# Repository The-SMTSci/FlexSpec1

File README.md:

# FlexSpec1

Small telescope Flexible Spectrograph One.

Check out the documentation: 

[FlexSpec1 ReadTheDocs.io](https://flexspec1.readthedocs.io/en/latest/)

History:
--------

V0.0 - pre-release placeholder.

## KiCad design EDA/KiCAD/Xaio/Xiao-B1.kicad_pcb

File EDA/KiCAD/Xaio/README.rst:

Xaio Standalone Board
=====================

Schematics
-----------

KiCAD Files
-----------

* XAIO-B1-A-cache.lib
* XAIO-B1-A-rescue.dcm
* XAIO-B1-A-rescue.lib
* Xiao-B1-cache.lib
* Xiao-B1.kicad_pcb
* Xiao-B1.pro
* Xiao-B1.sch
* Xiao-KM1-a-cache.lib
* Xiao-KM1-a-recover.pro
* Xiao-KM1-a.d356
* Xiao-KM1-a.kicad_pcb
* Xiao-KM1-a.pro
* sym-lib-table

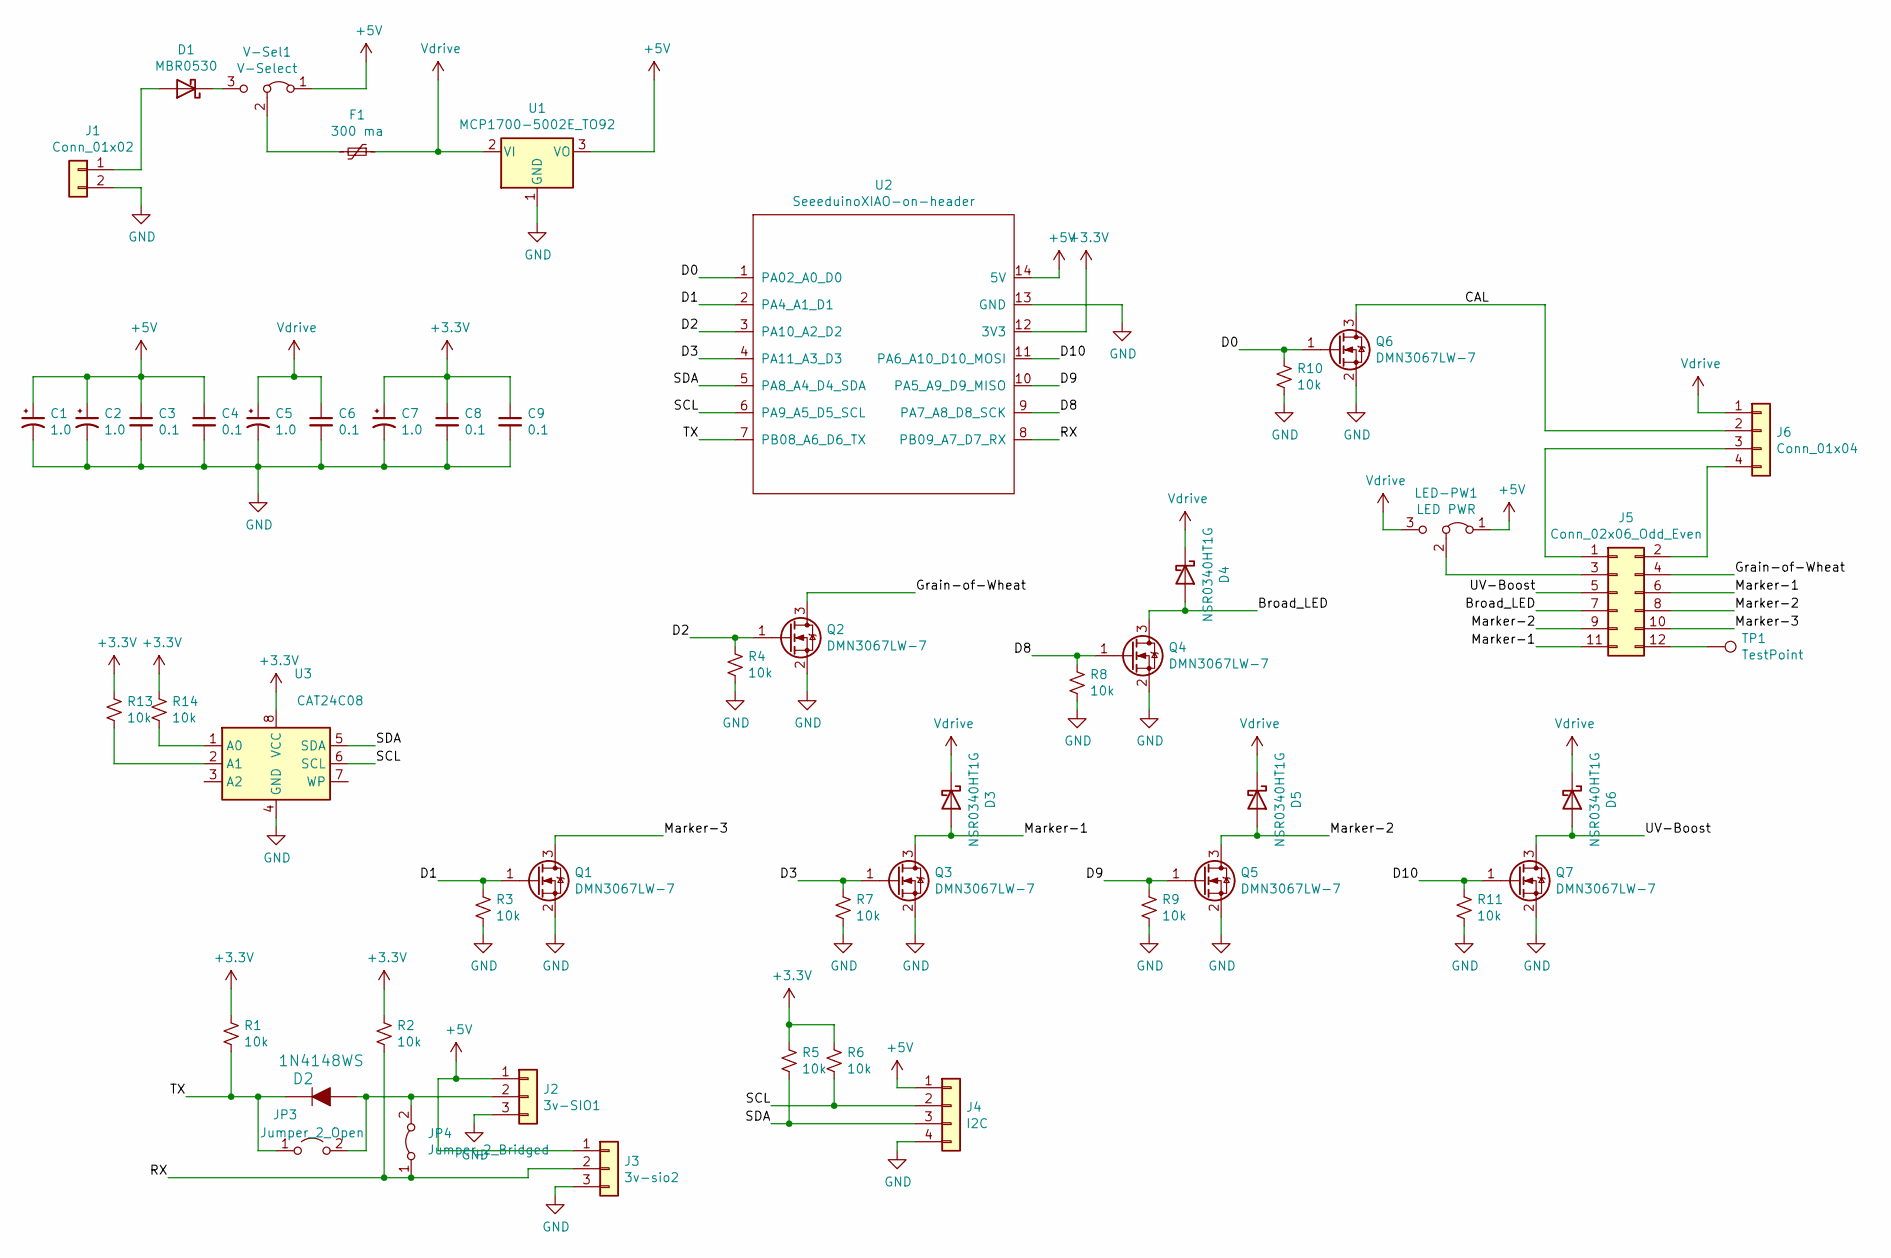
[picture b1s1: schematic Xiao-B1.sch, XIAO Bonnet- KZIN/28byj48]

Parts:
C1, C2, C5, C7: 1.0; C_0805_2012Metric_Pad1.18x1.45mm_HandSolder; MPN CL21A225KAFNNNE; JLCPCB C87994
C3, C4, C6, C8, C9: 0.1; C_0402_1005Metric_Pad0.74x0.62mm_HandSolder; MPN 0402X104K250CT; JLCPCB C237172
D1: MBR0530; D_SOD-123; MPN MBR0530; JLCPCB C475718
D2: 1N4148WS; SOD-323F; MPN 1N4148WS; Digi-Key_PN 1N4148WSFSCT-ND
D3, D4, D5, D6: NSR0340HT1G; D_SOD-323; MPN NSR0340HT1G; JLCPCB C90392
F1: 300 ma; Fuse_0805_2012Metric; MPN 0805L010/24YR; JLCPCB C207019
J1: Conn_01x02; PinHeader_1x02_P2.54mm_Vertical
J2: 3v-SIO1; Hirose_DF13-03P-1.25DSA_1x03_P1.25mm_Vertical; MPN 0530470310; Digi-Key_PN WM1732-ND
J3: 3v-sio2; Hirose_DF13-03P-1.25DSA_1x03_P1.25mm_Vertical; MPN 0530470310; Digi-Key_PN WM1732-ND
J4: I2C; Hirose_DF13-04P-1.25DSA_1x04_P1.25mm_Vertical; MPN 0530470410; Digi-Key_PN WM1733-ND
J5: Conn_02x06_Odd_Even; PinHeader_2x06_P2.54mm_Vertical; Mouser_PN 437-8038701020001101
J6: Conn_01x04; PinHeader_1x04_P2.54mm_Vertical
JP3: Jumper_2_Open; SolderJumper-2_P1.3mm_Open_Pad1.0x1.5mm
JP4: Jumper_2_Bridged; SolderJumper-2_P1.3mm_Bridged_Pad1.0x1.5mm
LED-PW1: LED PWR; SolderJumper-3_P1.3mm_Bridged12_Pad1.0x1.5mm_NumberLabels
Q1, Q2, Q3, Q4, Q5, Q6, Q7: DMN3067LW-7; SOT-323_SC-70_Handsoldering; MPN DMN3067LW-7; JLCPCB C212325
R1, R2, R3, R4, R5, R6, R7, R8, R9, R10, R11, R13, R14: 10k; R_0603_1608Metric_Pad0.98x0.95mm_HandSolder; MPN RC0603FR-0710KL; JLCPCB C98220
TP1: TestPoint; TestPoint_THTPad_1.0x1.0mm_Drill0.5mm
U1: MCP1700-5002E_TO92; TO-92_Inline
U2: SeeeduinoXIAO-on-header; Xiao-on-Header
U3: CAT24C08; TSSOP-8_4.4x3mm_P0.65mm; MPN CAT24C08YI-GT3; JLCPCB C193225
V-Sel1: V-Select; SolderJumper-3_P1.3mm_Bridged12_Pad1.0x1.5mm_NumberLabels

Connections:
+3V3: C7.1, C8.1, C9.1, R1.1, R2.1, R5.1, R6.1, R13.1, R14.1, U2.12 (3V3), U3.8 (VCC)
+5V: C1.1, C2.1, C3.1, C4.1, J2.1, J3.1, J4.1, LED-PW1.1 (A), U1.3 (VO), U2.14 (5V), V-Sel1.1 (A)
/Broad_LED: D4.2 (A), J5.7, Q4.3 (D)
/CAL: J6.2, Q6.3 (D)
/D0: Q6.1 (G), R10.1, U2.1 (PA02_A0_D0)
/D1: Q1.1 (G), R3.1, U2.2 (PA4_A1_D1)
/D2: Q2.1 (G), R4.1, U2.3 (PA10_A2_D2)
/D3: Q3.1 (G), R7.1, U2.4 (PA11_A3_D3)
/D8: Q4.1 (G), R8.1, U2.9 (PA7_A8_D8_SCK)
/D9: Q5.1 (G), R9.1, U2.10 (PA5_A9_D9_MISO)
/D10: Q7.1 (G), R11.1, U2.11 (PA6_A10_D10_MOSI)
/Grain-of-Wheat: J5.4, Q2.3 (D)
/Marker-1: D3.2 (A), J5.6, J5.11, Q3.3 (D)
/Marker-2: D5.2 (A), J5.8, J5.9, Q5.3 (D)
/Marker-3: J5.10, Q1.3 (D)
/RX: J3.2, JP4.1 (A), R2.2, U2.8 (PB09_A7_D7_RX)
/SCL: J4.2, R6.2, U2.6 (PA9_A5_D5_SCL), U3.6 (SCL)
/SDA: J4.3, R5.2, U2.5 (PA8_A4_D4_SDA), U3.5 (SDA)
/TX: D2.K, JP3.1 (A), R1.2, U2.7 (PB08_A6_D6_TX)
/UV-Boost: D6.2 (A), J5.5, Q7.3 (D)
GND: C1.2, C2.2, C3.2, C4.2, C5.2, C6.2, C7.2, C8.2, C9.2, J1.2, J2.3, J3.3, J4.4, Q1.2 (S), Q2.2 (S), Q3.2 (S), Q4.2 (S), Q5.2 (S), Q6.2 (S), Q7.2 (S), R3.2, R4.2, R7.2, R8.2, R9.2, R10.2, R11.2, U1.1 (GND), U2.13 (GND), U3.4 (GND)
unnamed: D1.1 (K), V-Sel1.3 (B)
unnamed: D1.2 (A), J1.1
unnamed: D2.A, J2.2, JP3.2 (B), JP4.2 (B)
unnamed: F1.2, V-Sel1.2 (C)
unnamed: J5.1, J6.3
unnamed: J5.2, J6.4
unnamed: J5.3, LED-PW1.2 (C)
unnamed: J5.12, TP1.1
unnamed: R13.2, U3.2 (A1)
unnamed: R14.2, U3.1 (A0)
Vdrive: C5.1, C6.1, D3.1 (K), D4.1 (K), D5.1 (K), D6.1 (K), F1.1, J6.1, LED-PW1.3 (B), U1.2 (VI)

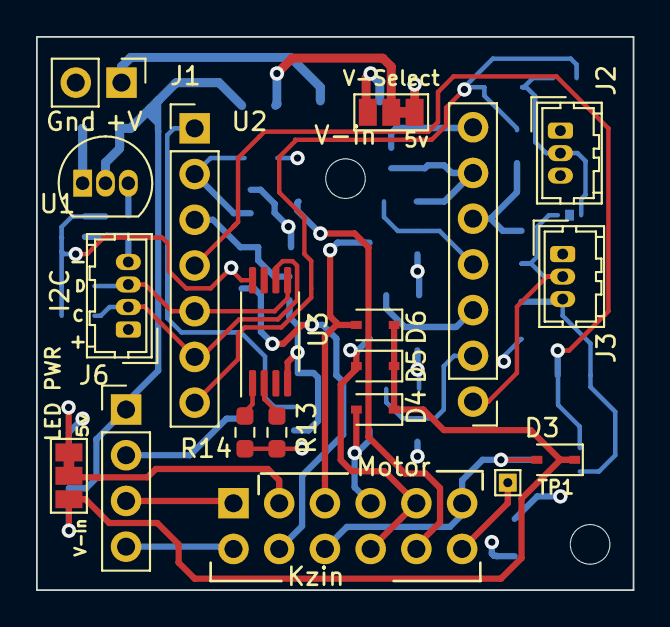
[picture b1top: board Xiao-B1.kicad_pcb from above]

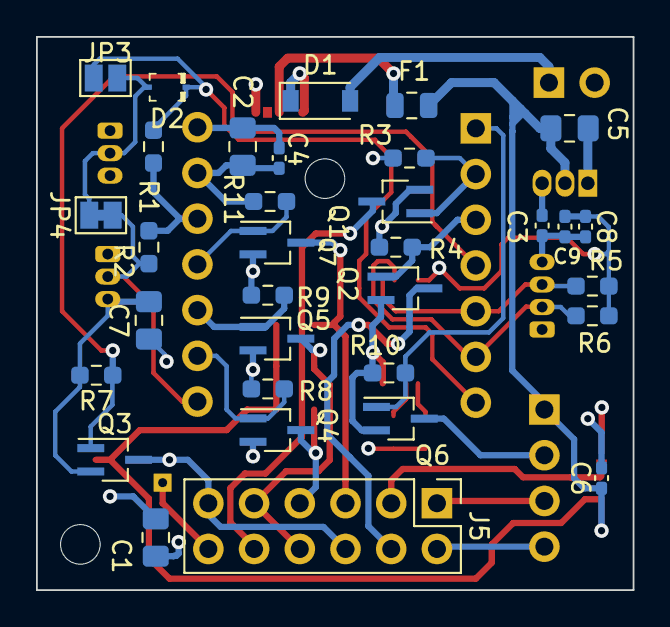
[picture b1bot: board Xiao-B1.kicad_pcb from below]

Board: 4 copper layers, 33.1 x 30.7 mm, 52 parts (33 on the bottom side), 32 nets.

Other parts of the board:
M: MountingHole_2.2mm_M2
M#2: MountingHole_2.2mm_M2

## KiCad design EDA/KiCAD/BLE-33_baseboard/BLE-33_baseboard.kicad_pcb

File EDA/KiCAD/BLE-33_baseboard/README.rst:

EDA BLE-33 Baseboard
====================

Schematics
----------

   * BLE-33_baseboard-v2.pdf
   * BLE-33_baseboard-build-1.pdf

KiCAD Files
-----------

   * BLE-33_baseboard-cache.lib
   * BLE-33_baseboard.d356
   * BLE-33_baseboard.kicad_pcb
   * BLE-33_baseboard.pro
   * BLE-33_baseboard.sch
   * BLE-33_baseboard.step
   * BLE-33_baseboard.wrl
   * Fab_files
   * _autosave-BLE-33_baseboard.pro

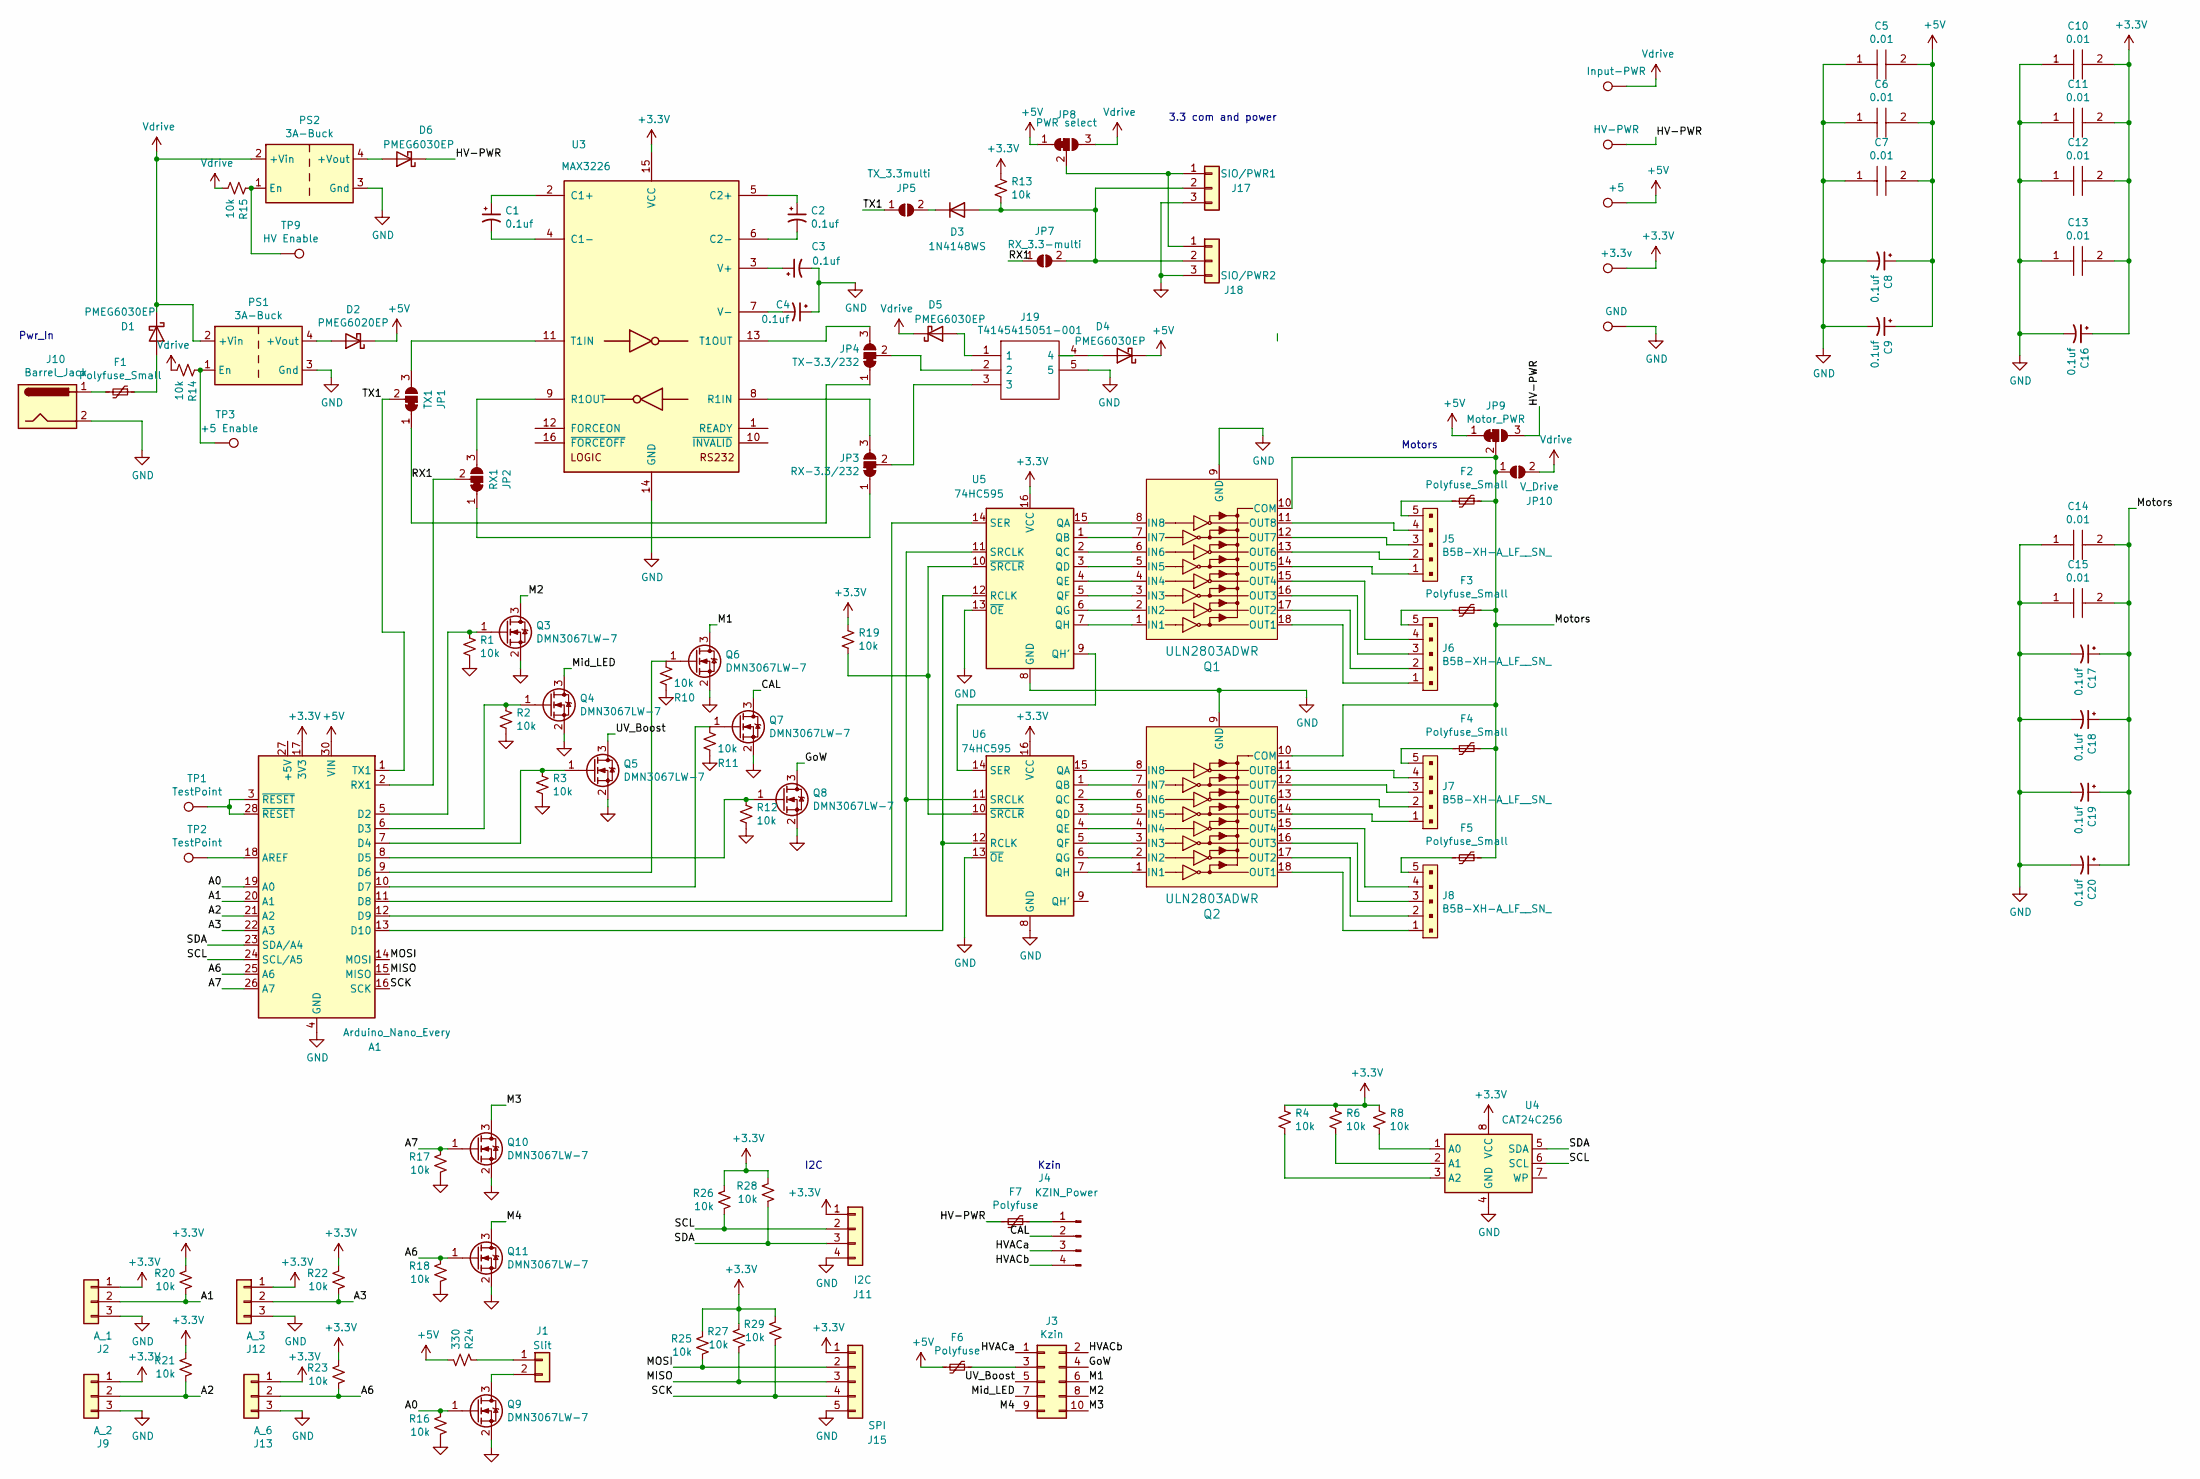
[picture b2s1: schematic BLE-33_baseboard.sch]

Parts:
A1: Arduino_Nano_Every; Arduino_Nano
C1, C2, C3, C4: 0.1uf; C_0805_2012Metric; MPN TAJR104M035RNJ; Digi-Key_PN 478-11592-1-ND
C5, C6, C7, C10, C11, C12, C13, C14, C15: 0.01; CAPC1608X90N; Manufacturer_Part_Number CGA3E2X7R1H103K080AA; Mouser Part Number 810-CGA3E2X7R1H103K
C8, C9, C16, C17, C18, C19, C20: 0.1uf; C_0805_2012Metric; MPN TAJR104M035RNJ; Digi-Key 478-11592-1-ND
D1: PMEG6030EP; D_SOD-128
D2: PMEG6020EP; D_SOD-128; MPN PMEG6030EP/8X; Digi-Key 1727-7646-1-ND
D3: 1N4148WS; D_SOD-323
D4, D6: PMEG6030EP; D_SOD-128; MPN PMEG6030EP/8X; Digi-Key 1727-7646-1-ND
D5: PMEG6030EP; D_SOD-128; MPN PMEG6030EP/8X; Digi-Key_PN 1727-7646-1-ND
F1: Polyfuse_Small; Fuse_1206_3216Metric; MPN 0ZCJ0075AF2E; Digi-Key 507-1805-1-ND
F2, F3, F4, F5: Polyfuse_Small; Fuse_0805_2012Metric; MPN 0805L020YR; Digi-Key F2770CT-ND
F6, F7: Polyfuse; Fuse_0805_2012Metric; MPN 0805L020YR; Digi-Key F2770CT-ND
J1: Slit; Hirose_DF13-02P-1.25DSA_1x02_P1.25mm_Vertical; MPN 0530470210; Digi-Key WM1731-ND
J2: A_1; Hirose_DF13-03P-1.25DSA_1x03_P1.25mm_Vertical; Digi-Key WM1732-ND
J3: Kzin; PinHeader_2x05_P2.54mm_Horizontal; Digi-Key 10129382-910004BLF-ND
J4: KZIN_Power; PinHeader_1x04_P2.54mm_Horizontal; Digi-Key WM4302-ND
J5, J6, J7, J8: B5B-XH-A_LF__SN_; JST_XH_B5B-XH-AM_1x05_P2.50mm_Vertical; MPN B5B-XH-AM(LF)(SN); Digi-Key 455-2239-ND
J9: A_2; Hirose_DF13-03P-1.25DSA_1x03_P1.25mm_Vertical; Digi-Key WM1732-ND
J10: Barrel_Jack; BarrelJack_CUI_PJ-063AH_Horizontal_CircularHoles; MPN PJ-063AH; Digi-Key CP-063AH-ND
J11: I2C; Molex_PicoBlade_53047-0410_1x04_P1.25mm_Vertical; Digi-Key WM1733-ND
J12: A_3; Hirose_DF13-03P-1.25DSA_1x03_P1.25mm_Vertical; Digi-Key WM1732-ND
J13: A_6; Hirose_DF13-03P-1.25DSA_1x03_P1.25mm_Vertical; Digi-Key WM1732-ND
J15: SPI; Molex_PicoBlade_53047-0510_1x05_P1.25mm_Vertical; Digi-Key WM1734-ND
J17: SIO/PWR1; Hirose_DF13-03P-1.25DSA_1x03_P1.25mm_Vertical; Digi-Key WM1732-ND
J18: SIO/PWR2; Hirose_DF13-03P-1.25DSA_1x03_P1.25mm_Vertical; Digi-Key WM1732-ND
J19: T4145415051-001; T4145415051001; Manufacturer_Part_Number T4145415051-001; Mouser Part Number 571-T4145415051-001
JP1: TX1; SolderJumper-3_P1.3mm_Bridged12_RoundedPad1.0x1.5mm_NumberL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
JP2: RX1; SolderJumper-3_P1.3mm_Bridged12_RoundedPad1.0x1.5mm_NumberL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
JP3: RX-3.3/232; SolderJumper-3_P1.3mm_Bridged12_RoundedPad1.0x1.5mm_NumberL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
JP4: TX-3.3/232; SolderJumper-3_P1.3mm_Bridged12_RoundedPad1.0x1.5mm_NumberL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
JP5: TX_3.3multi; SolderJumper-2_P1.3mm_Open_Pad1.0x1.5mm
JP7: RX_3.3-multi; SolderJumper-2_P1.3mm_Open_Pad1.0x1.5mm
JP8: PWR select; SolderJumper-3_P1.3mm_Bridged12_RoundedPad1.0x1.5mm_NumberL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
JP9: Motor_PWR; SolderJumper-3_P1.3mm_Bridged12_RoundedPad1.0x1.5mm_NumberL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
JP10: V_Drive; SolderJumper-2_P1.3mm_Open_Pad1.0x1.5mm
PS1, PS2: 3A-Buck; Converter_DCDC_3A-Buck
Q1, Q2: ULN2803ADWR; SOIC-18_W7.5mm; MPN ULN2803ADWR; Digi-Key 296-15777-1-ND
Q3, Q4, Q5, Q6, Q7, Q8, Q9, Q10, Q11: DMN3067LW-7; SOT-323_SC-70; MPN DMN3067LW-7; Digi-Key DMN3067LW-7DICT-ND
R1, R2, R3, R4, R6, R8, R10, R11, R12, R13, R14, R16, R17, R18, R19, R20, R21, R22, R23, R25, R26, R27, R28, R29: 10k; R_0805_2012Metric; MPN SR0805JR-0710KL; Digi-Key 13-SR0805JR-0710KLCT-ND
R15: 10k; R_0805_2012Metric; MPN SR0805JR-0710KL; Digi-Key_PN 13-SR0805JR-0710KLCT-ND
R24: 330; R_1206_3216Metric
TP1, TP2: TestPoint; TestPoint_THTPad_D1.0mm_Drill0.5mm
TP3: +5 Enable; TestPoint_THTPad_D1.0mm_Drill0.5mm
TP4: HV-PWR; TestPoint_THTPad_D1.0mm_Drill0.5mm
TP5: +5; TestPoint_THTPad_D1.0mm_Drill0.5mm
TP6: +3.3v; TestPoint_THTPad_D1.0mm_Drill0.5mm
TP7: GND; TestPoint_THTPad_D1.0mm_Drill0.5mm
TP8: Input-PWR; TestPoint_THTPad_D1.0mm_Drill0.5mm
TP9: HV Enable; TestPoint_THTPad_D1.0mm_Drill0.5mm
U3: MAX3226; SSOP-16_5.3x6.2mm_P0.65mm; MPN MAX3226CAE+; Digi-Key MAX3226CAE+-ND
U4: CAT24C256; TSSOP-8_4.4x3mm_P0.65mm; MPN CAT24C256YI-GT3; Digi-Key CAT24C256YI-GT3OSCT-ND - Cut Tape (CT)
U5, U6: 74HC595; SSOP-16_4.4x5.2mm_P0.65mm; MPN SN74HC595ADB; Digi-Key 2156-SN74HC595ADB-ND

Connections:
+3V3: A1.17 (3V3), C10.2, C11.2, C12.2, C13.2, C16.1, J2.1, J9.1, J11.1, J12.1, J13.1, J15.1, R4.1, R6.1, R8.1, R13.1, R19.1, R20.1, R21.1, R22.1, R23.1, R25.1, R26.1, R27.1, R28.1, R29.1, TP6.1, U3.15 (VCC), U4.8 (VCC), U5.16 (VCC), U6.16 (VCC)
+5V: A1.30 (VIN), C5.2, C6.2, C7.2, C8.1, C9.1, D2.1 (K), D4.1 (K), F6.2, JP8.1 (A), JP9.1 (A), R24.2, TP5.1
/A0: A1.19 (A0), Q9.1 (G), R16.1
/A1: A1.20 (A1), J2.2, R20.2
/A2: A1.21 (A2), J9.2, R21.2
/A3: A1.22 (A3), J12.2, R22.2
/A6: A1.25 (A6), J13.2, Q11.1 (G), R18.1, R23.2
/A7: A1.26 (A7), Q10.1 (G), R17.1
/CAL: J4.2, Q7.3 (D)
/GoW: J3.4, Q8.3 (D)
/HV-PWR: D6.1 (K), F7.2, JP9.3 (B), TP4.1
/HVACa: J3.1, J4.3
/HVACb: J3.2, J4.4
/M1: J3.6, Q6.3 (D)
/M2: J3.8, Q3.3 (D)
/M3: J3.10, Q10.3 (D)
/M4: J3.9, Q11.3 (D)
/MISO: A1.15 (MISO), J15.3, R27.2
/MOSI: A1.14 (MOSI), J15.2, R25.2
/Mid_LED: J3.7, Q4.3 (D)
/Motors: C14.2, C15.2, C17.1, C18.1, C19.1, C20.1, F2.1, F3.1, F4.1, F5.1, JP9.2 (C), JP10.1 (A), Q1.10 (COM), Q2.10 (COM)
/RX1: A1.2 (RX1), JP2.2 (C), JP7.1 (A)
/SCK: A1.16 (SCK), J15.4, R29.2
/SCL: A1.24 (SCL/A5), J11.2, R26.2, U4.6 (SCL)
/SDA: A1.23 (SDA/A4), J11.3, R28.2, U4.5 (SDA)
/TX1: A1.1 (TX1), JP1.2 (C), JP5.1 (A)
/UV_Boost: J3.5, Q5.3 (D)
GND: A1.4 (GND), A1.29 (GND), C3.2, C4.1, C5.1, C6.1, C7.1, C8.2, C9.2, C10.1, C11.1, C12.1, C13.1, C14.1, C15.1, C16.2, C17.2, C18.2, C19.2, C20.2, J2.3, J9.3, J10.2, J11.4, J12.3, J13.3, J15.5, J17.3, J18.3, J19.5, PS1.3 (Gnd), PS2.3 (Gnd), Q1.9 (GND), Q2.9 (GND), Q3.2 (S), Q4.2 (S), Q5.2 (S), Q6.2 (S), Q7.2 (S), Q8.2 (S), Q9.2 (S), Q10.2 (S), Q11.2 (S), R1.2, R2.2, R3.2, R10.2, R11.2, R12.2, R16.2, R17.2, R18.2, TP7.1, U3.14 (GND), U4.4 (GND), U5.8 (GND), U5.13 (~OE), U6.8 (GND), U6.13 (~OE)
unnamed: A1.5 (D2), Q3.1 (G), R1.1
unnamed: A1.6 (D3), Q4.1 (G), R2.1
unnamed: A1.7 (D4), Q5.1 (G), R3.1
unnamed: A1.8 (D5), Q8.1 (G), R12.1
unnamed: A1.9 (D6), Q6.1 (G), R10.1
unnamed: A1.10 (D7), Q7.1 (G), R11.1
unnamed: A1.11 (D8), U5.14 (SER)
unnamed: A1.12 (D9), U5.11 (SRCLK), U6.11 (SRCLK)
unnamed: A1.13 (D10), U5.12 (RCLK), U6.12 (RCLK)
unnamed: A1.18 (AREF), TP2.1
unnamed: A1.3 (~RESET), A1.28 (~RESET), TP1.1
unnamed: C1.1, U3.2 (C1+)
unnamed: C1.2, U3.4 (C1-)
unnamed: C2.1, U3.5 (C2+)
unnamed: C2.2, U3.6 (C2-)
unnamed: C3.1, U3.3 (V+)
unnamed: C4.2, U3.7 (V-)
unnamed: D1.2 (A), F1.1
unnamed: D2.2 (A), PS1.4 (+Vout)
unnamed: D3.1 (K), JP5.2 (B)
unnamed: D3.2 (A), J17.2, J18.2, JP7.2 (B), R13.2
unnamed: D4.2 (A), J19.4
unnamed: D5.2 (A), J19.1
unnamed: D6.2 (A), PS2.4 (+Vout)
unnamed: F1.2, J10.1
unnamed: F2.2, J5.5
unnamed: F3.2, J6.5
unnamed: F4.2, J7.5
unnamed: F5.2, J8.5
unnamed: F6.1, J3.3
unnamed: F7.1, J4.1
unnamed: J1.1, R24.1
unnamed: J1.2, Q9.3 (D)
unnamed: J5.1, Q1.14 (OUT5)
unnamed: J5.2, Q1.13 (OUT6)
unnamed: J5.3, Q1.12 (OUT7)
unnamed: J5.4, Q1.11 (OUT8)
unnamed: J6.1, Q1.18 (OUT1)
unnamed: J6.2, Q1.17 (OUT2)
unnamed: J6.3, Q1.16 (OUT3)
unnamed: J6.4, Q1.15 (OUT4)
unnamed: J7.1, Q2.14 (OUT5)
unnamed: J7.2, Q2.13 (OUT6)
unnamed: J7.3, Q2.12 (OUT7)
unnamed: J7.4, Q2.11 (OUT8)
unnamed: J8.1, Q2.18 (OUT1)
unnamed: J8.2, Q2.17 (OUT2)
unnamed: J8.3, Q2.16 (OUT3)
unnamed: J8.4, Q2.15 (OUT4)
unnamed: J17.1, J18.1, JP8.2 (C)
unnamed: J19.2, JP4.2 (C)
unnamed: J19.3, JP3.2 (C)
unnamed: JP1.1 (A), JP4.1 (A)
unnamed: JP1.3 (B), U3.11 (T1IN)
unnamed: JP2.1 (A), JP3.1 (A)
unnamed: JP2.3 (B), U3.9 (R1OUT)
unnamed: JP3.3 (B), U3.8 (R1IN)
unnamed: JP4.3 (B), U3.13 (T1OUT)
unnamed: PS1.1 (En), R14.1, TP3.1
unnamed: PS2.1 (En), R15.1, TP9.1
unnamed: Q1.1 (IN1), U5.7 (QH)
unnamed: Q1.2 (IN2), U5.6 (QG)
unnamed: Q1.3 (IN3), U5.5 (QF)
unnamed: Q1.4 (IN4), U5.4 (QE)
unnamed: Q1.5 (IN5), U5.3 (QD)
unnamed: Q1.6 (IN6), U5.2 (QC)
unnamed: Q1.7 (IN7), U5.1 (QB)
unnamed: Q1.8 (IN8), U5.15 (QA)
unnamed: Q2.1 (IN1), U6.7 (QH)
unnamed: Q2.2 (IN2), U6.6 (QG)
unnamed: Q2.3 (IN3), U6.5 (QF)
unnamed: Q2.4 (IN4), U6.4 (QE)
unnamed: Q2.5 (IN5), U6.3 (QD)
unnamed: Q2.6 (IN6), U6.2 (QC)
unnamed: Q2.7 (IN7), U6.1 (QB)
unnamed: Q2.8 (IN8), U6.15 (QA)
unnamed: R4.2, U4.3 (A2)
unnamed: R6.2, U4.2 (A1)
unnamed: R8.2, U4.1 (A0)
unnamed: R19.2, U5.10 (~SRCLR), U6.10 (~SRCLR)
unnamed: U5.9 (QH'), U6.14 (SER)
Vdrive: D1.1 (K), D5.1 (K), JP8.3 (B), JP10.2 (B), PS1.2 (+Vin), PS2.2 (+Vin), R14.2, R15.2, TP8.1

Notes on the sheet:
Pwr_In
Motors
I2C
Kzin
3.3 com and power

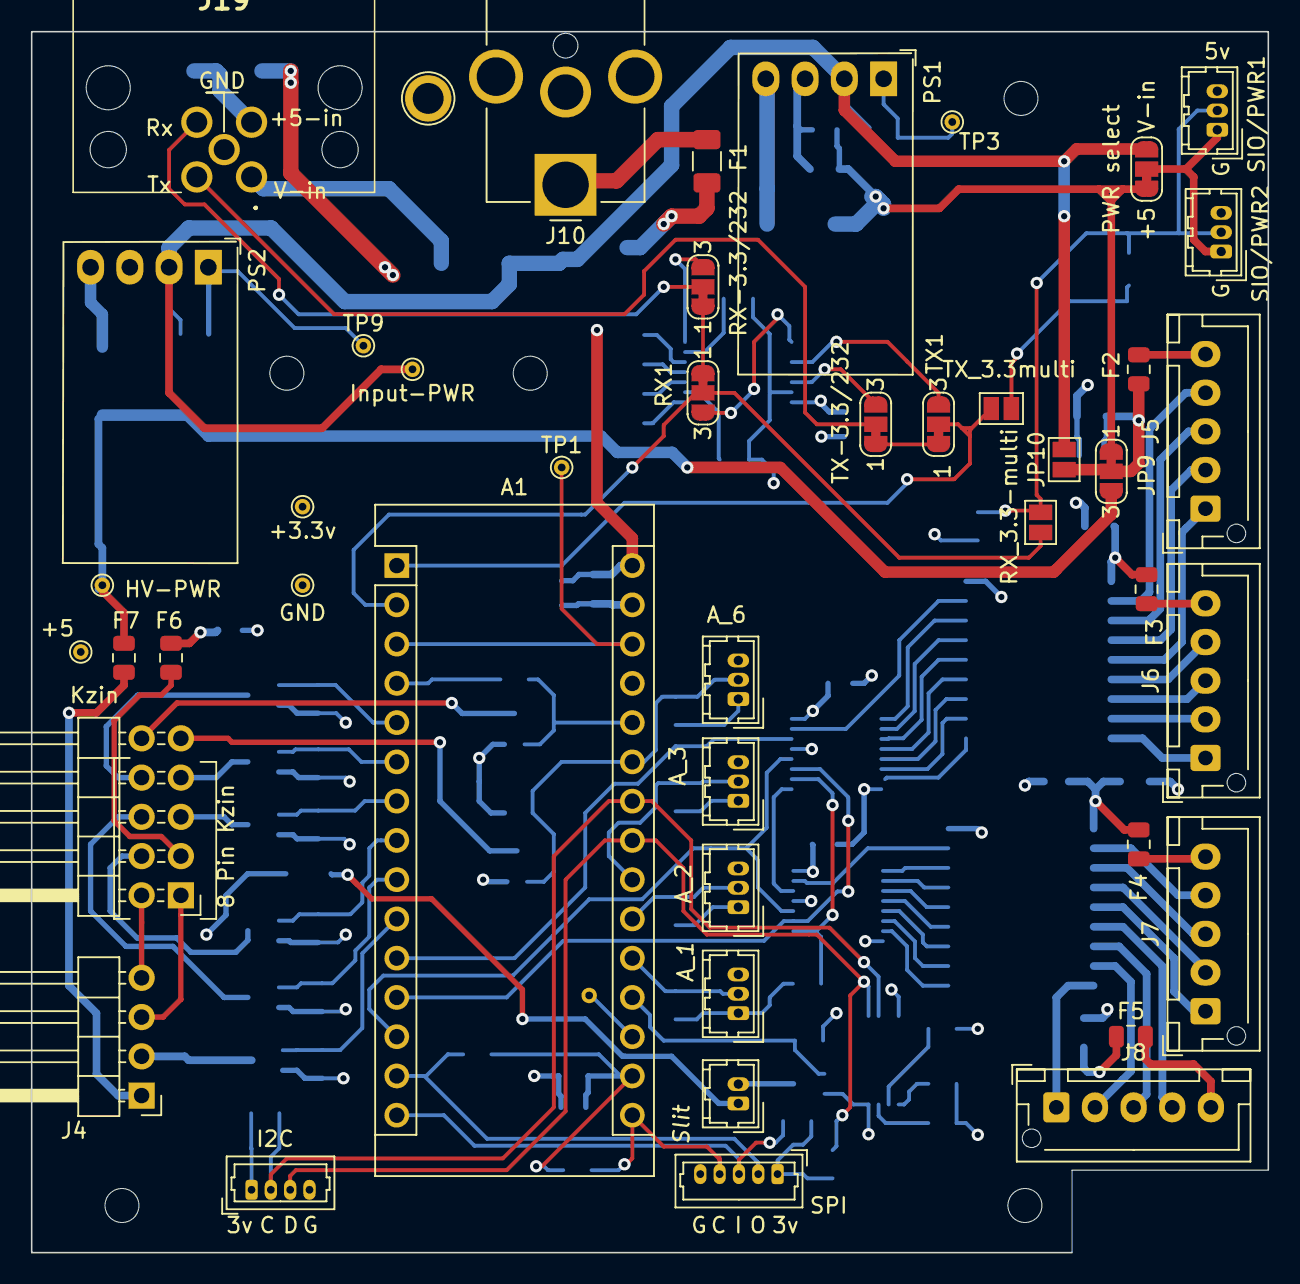
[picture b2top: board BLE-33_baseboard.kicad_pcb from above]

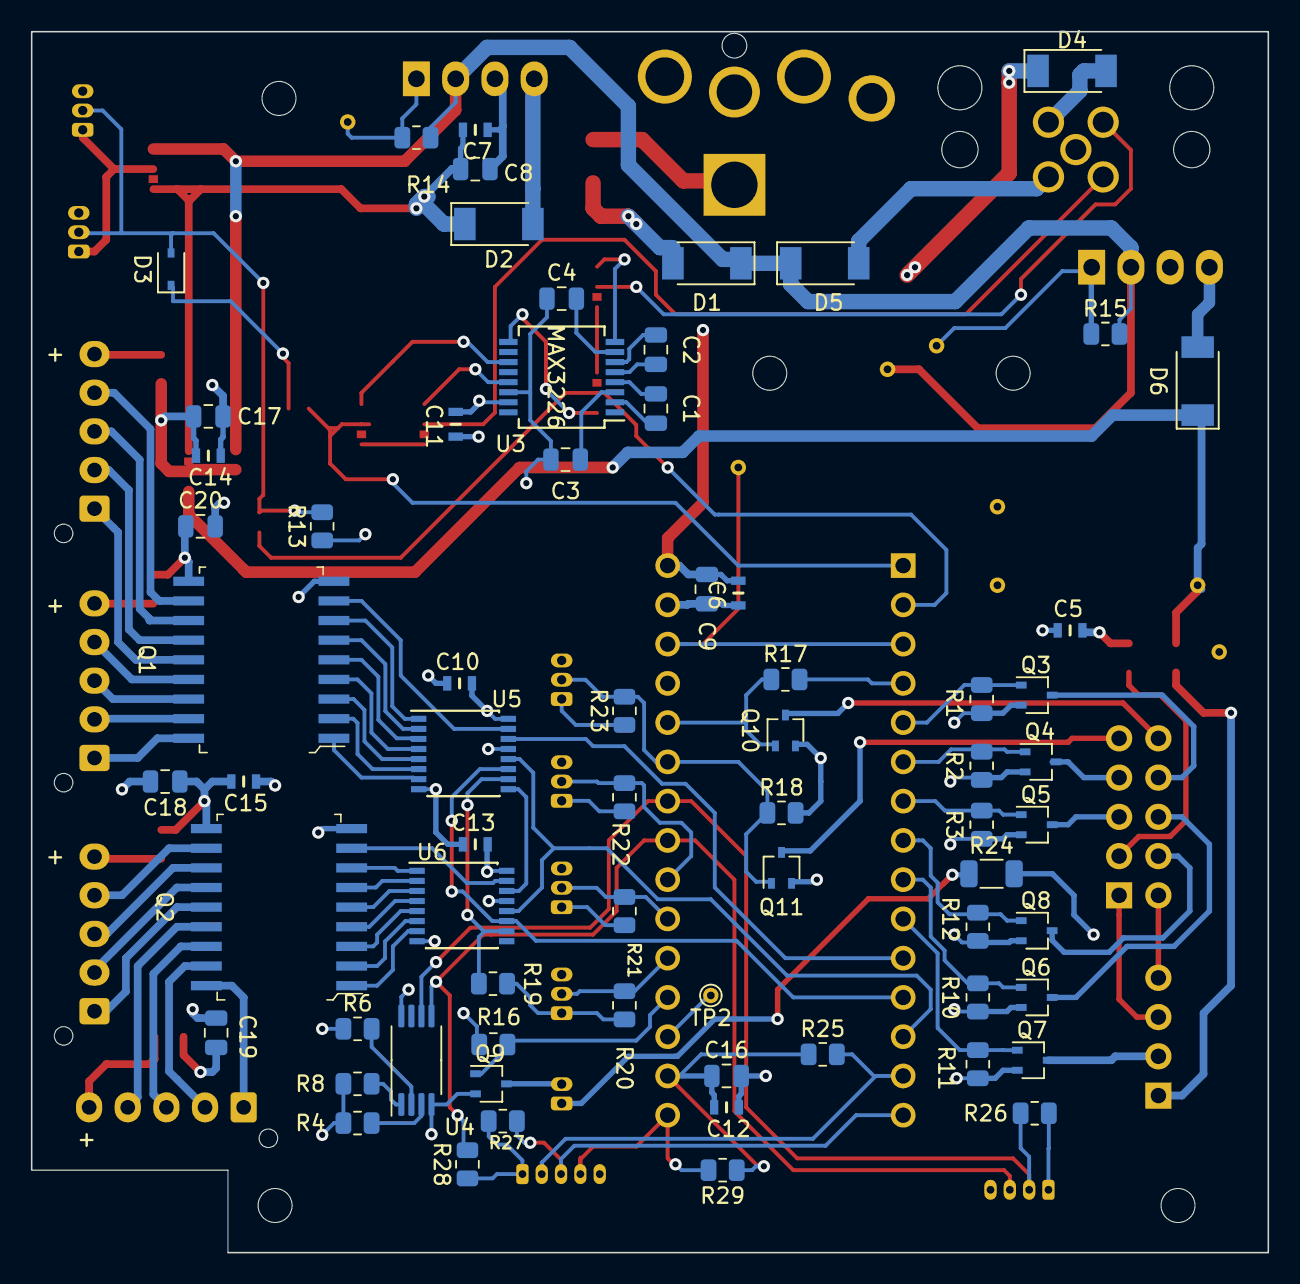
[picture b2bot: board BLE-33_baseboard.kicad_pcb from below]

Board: 4 copper layers, 80.0 x 79.0 mm, 112 parts (68 on the bottom side), 110 nets.

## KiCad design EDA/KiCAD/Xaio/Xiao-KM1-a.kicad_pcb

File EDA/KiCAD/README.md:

README
======

Directories herein contain various schematics for the project.

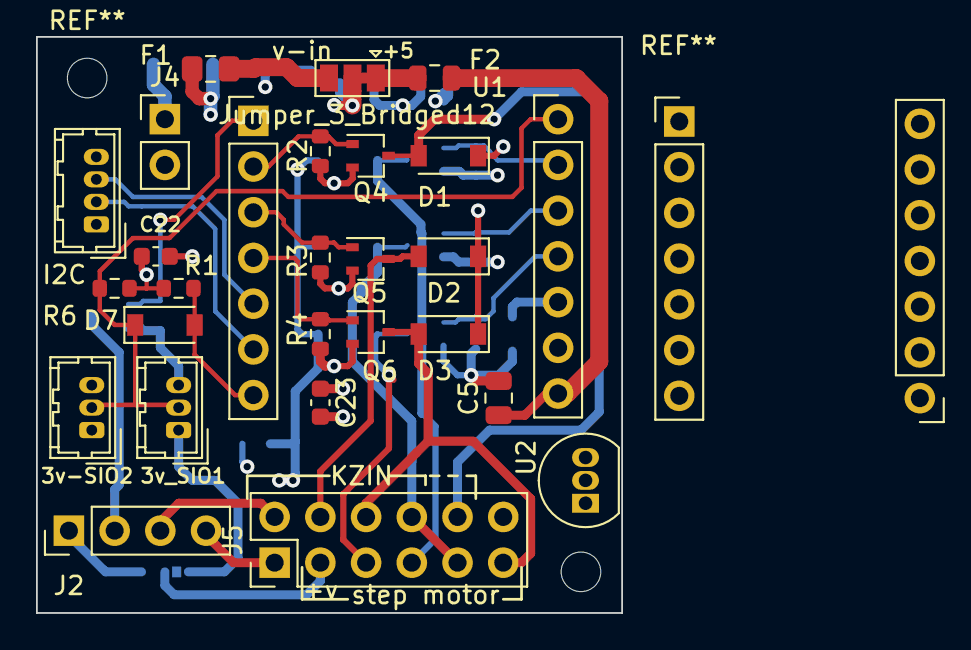
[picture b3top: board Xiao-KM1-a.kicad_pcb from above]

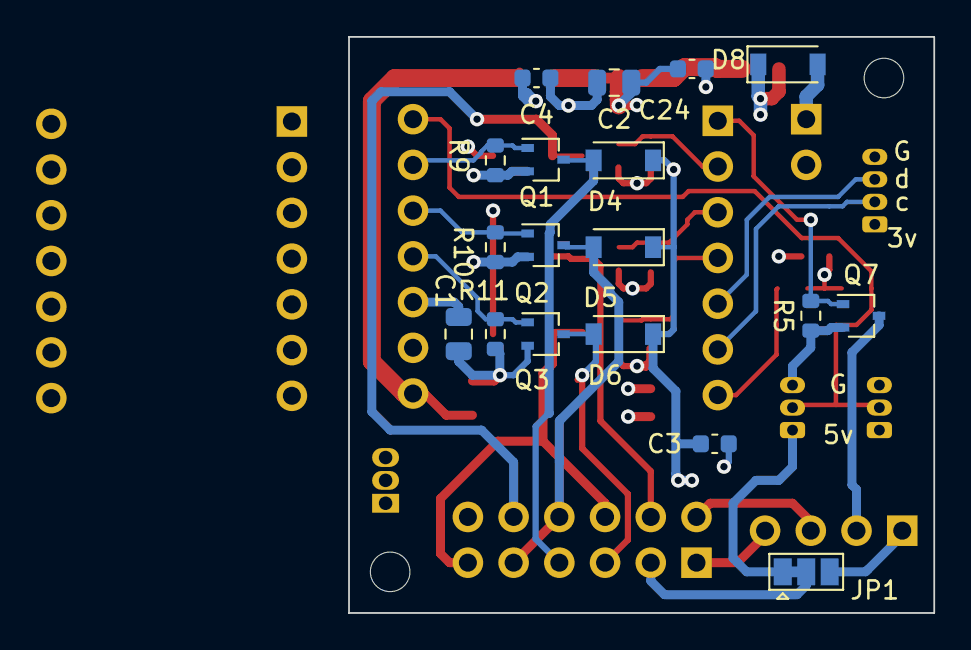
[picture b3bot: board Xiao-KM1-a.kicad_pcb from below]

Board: 4 copper layers, 32.5 x 32.0 mm, 44 parts (18 on the bottom side), 29 nets.

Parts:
C1, C2, C5: TAJR104M035RNJ; C_0805_2012Metric
C3, C4, C22, C23, C24: .01; C_0603_1608Metric
D1, D2, D3, D4, D5, D6, D8: MBR0580; D_SOD-123
D7: 1N4148W; D_SOD-123
F1: 500ma; Fuse_0805_2012Metric_Pad1.15x1.40mm_HandSolder
F2: Polyfuse- 350 ma; Fuse_0805_2012Metric
J1: I2C; Hirose_DF13-04P-1.25DSA_1x04_P1.25mm_Vertical
J2: Cal_PS; PinHeader_1x04_P2.54mm_Vertical
J3: 3v_SIO1; Hirose_DF13-03P-1.25DSA_1x03_P1.25mm_Vertical
J4: 277-6156-ND; PinHeader_1x02_P2.54mm_Vertical
J5: Conn_02x06_Odd_Even; PinHeader_2x06_P2.54mm_Vertical
J6: 3v-SIO2; Hirose_DF13-03P-1.25DSA_1x03_P1.25mm_Vertical
JP1, JP2: Jumper_3_Bridged12; SolderJumper-3_P1.3mm_Bridged12_Pad1.0x1.5mm
Q1, Q2, Q3, Q4, Q5, Q6, Q7: DMN3067; SOT-323_SC-70
R1, R2, R3, R4, R5, R6, R9, R10, R11: 10,000; R_0603_1608Metric
U1: SeeeduinoXIAO-on-header; Xiao-on-socket
U2: MCP1700-5002E_TO92; TO-92_Inline

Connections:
+3V3: C1.1, C22.1, C23.1, J1.1, R1.2, R6.1, U1.12
+5V: C4.1, C5.1, F2.2, J3.1, J6.1, JP1.1, U1.14, U2.3
/Broad_LED: D4.2, J5.7, Q1.3
/Cal_HV1: J2.4, J5.1
/Cal_HV2: J2.3, J5.2
/Cal_Lamp: J2.2, Q7.3
/GPIO_0: Q7.1, R5.1, U1.1
/GPIO_1: Q4.1, R2.1, U1.2
/GPIO_2: Q5.1, R3.1, U1.3
/GPIO_3: Q6.1, R4.1, U1.4
/GPIO_4: J1.3, U1.5
/GPIO_5: J1.2, U1.6
/GPIO_8: Q1.1, R9.1, U1.9
/GPIO_9: Q2.1, R10.1, U1.10
/GPIO_10: Q3.1, R11.1, U1.11
/Grain_of_Wheat: D2.2, J5.4, Q5.3
/MOTOR_POWER-IN: D8.1, F1.2
/Marker-1: D3.2, J5.6, J5.11, Q6.3
/Marker-2: D5.2, J5.8, J5.9, Q2.3
/Marker-3: D1.2, J5.10, Q4.3
/UART_RX: D7.1, J3.2, J6.2, R6.2, U1.8
/UART_TX: D7.2, R1.1, U1.7
/UV-Boost: D6.2, J5.5, Q3.3
GND: C1.2, C2.2, C3.2, C4.2, C5.2, C22.2, C23.2, C24.2, J1.4, J3.3, J4.2, J6.3, Q1.2, Q2.2, Q3.2, Q4.2, Q5.2, Q6.2, Q7.2, R2.2, R3.2, R4.2, R5.2, R9.2, R10.2, R11.2, U1.13, U2.1
Motor_PWR: C2.1, C3.1, C24.1, D1.1, D2.1, D3.1, D4.1, D5.1, D6.1, J2.1, JP1.3, JP2.2, U2.2
unnamed: D8.2, J4.1
unnamed: F1.1, JP2.3
unnamed: F2.1, JP2.1
unnamed: J5.3, JP1.2

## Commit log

2021-03-27 Adding the hook for SASFS1 to readthedocs.io
2021-03-27 Fixed NA1 to FS1
2021-04-01 Renaming the thing from FS1 to FlexSpec1
2021-04-01 Changing the projec name to FlexSpec1
2021-04-01 Changend link name from SASFS1 to FlexSpec1 for readthedocs.io
2021-04-01 Still tracking FS1/NA1 details
2021-04-08 Added notice of status.
2021-04-08 Finessed the readthedocs location.
2021-04-08 Opls left part off.
2021-06-17 Name up-to-date;; HISTORY
2021-06-21 Incremental Checkin for FS1
2021-06-21 Incremental checkin
2021-06-21 Fixing abstract
2021-06-21 Hacked index back into existance, cleaned html doc build
2021-06-21 Adding code to the mix
2021-06-21 Added the docker snapshot
2021-06-21 Added the EDA aspect
2021-06-28 Found a few typos with the Grating module, and added code to keep any previous cwave.
2021-06-29 Updated the info on using arduinos
2021-07-16 Created a Kzin class specifically for that device, with sliders for intensity 0..100%. Modified FlexSpec.py to use the new KzinBokey module
2021-07-16 Incremental
2021-07-16 Mived the UI code into its own subdirectory
2021-07-16 removed the old files from this location
2021-07-17 Dang, I spelt 'receipt' wrong.
2021-07-17 Changed size of Kzin buttons, spelling, layout minor updates.
2021-07-17 Added link to the readthedocs documentation
2021-07-21 Fixed a call by reference (doesn't work) with a dictionary enbedded in an instance class. The class may support error checking in future.
2021-07-21 Added a stub of server.
2021-08-22 Sync my state with the world. Tweaks to the server.
2021-08-24 Adding the bin dir and a runflexspec command
2021-08-25 Added the aliases for the terminal on the pi
2021-08-27 Changed the message across the board to be right and consistent. Handled the home with a simple state variable. Updated the server, tested a bit more this time.
2021-09-14 Error in bash script, missing ;; for a case.
2021-09-23 Added a GratingDefinitions.py file, with the Edmund and Thorlabs grating definitions, in anticipation of a Factory C++ method and a Bokeh composer for user's specific gratings.
2021-09-29 Added launcher capable runflexspec and added a linux ico for task.
2022-01-01 Incremental update with modified, updated c++ code.
2022-01-02 Oops checkin ahead of schedule
2022-01-02 Clean up ELF checkins and some pre-compiled files
2022-01-02 More clean up
2022-02-24 Removed 'orientation' from the radio group
2022-03-06 Copied from working dir, added License/README
2022-03-06 The license and readme files.
2022-03-06 fixed README
2022-03-06 Prettyfied README
2022-03-06 replaced wrong version
2022-03-08 Changed core to class
2022-03-13 Completed IMU/ParallacticAngle
2022-03-14 Renamed server, added shutter
2022-03-18 Missing Shutter, added dockerfile
2022-03-24 Added Shutter.py to the mix
2022-03-25 Started moving the docs to the new 2022 paper. Added the shutter mechanism for Bokeh.
2022-04-11 Additional Images
    Additional Images
2022-04-11 Further diagrams
2022-04-19 Added -p to report port in use, added code to kill the task and reinitiate if already running.
2022-04-21 Fixing the ovio.rst file.
2022-04-21 Fixing filenames with spaces.
2022-04-21 fixing filenames
2022-04-21 Adding placeholders
2022-04-21 adding them all.
2022-04-21 Added _static to the html_static_path
2022-04-21 Spelling error
2022-04-22 Added section for kzin ring
2022-04-22 Getting pix to work
2022-05-19 Named the PostmasterServer for what it is. Added a few files for git, protocol, sextractor and changed a few for clarity.
2022-07-17 Added a driectory for Tools, for spreadsheets, and other tooly things.
2022-07-17 Moved to tools, removed spaces in file name.
2022-07-17 Duplicate removed
2022-07-17 added .gitignore to ignore sphinx intermediate files.
2022-07-17 Removing intermediate sphinx files.
2022-07-17 Removing sphinx intermediate files.
2022-07-17 Adding all the images.
2022-07-17 Added a readme
2022-07-17 Added updated rst files. Especially for the eeprom, glossary and parallactic angle.
2022-07-22 Added/fixed docs. EEPROM ideas in particular.
2022-07-22 Added EEPROM basic code for handling the contents of the main json string back from the eeprom device.
2022-07-22 Caught a constant error in physics
2022-07-23 Added a few gitignores.
2022-07-23 Matched the docs with the private dir. make a clean sphinx make.
2022-08-06 Adjusting a few ints to strings; changed Display comment to python for generic; Fixed the Grating -- the class was built from slit, and had a few incongruous things.
2022-08-09 Unification of the code, adjusting variables to reflect what they actually do. Display.py is replaced with the virtually identical FlexPublish.py to have the filename reflect what it does, and to sta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
    Error handling was beefed up a bit, some dead code removed.
    Comments were fixed from a fast cut/paste approach early on
    to have the comments actually mean something for thier code.
    Some pythonic typing was added. Dunder's added in some places,
    more to do.
    The tabs were renamed in FlexSpec.py to reflect the actual
2022-09-13 Added a vimrc for user.
2022-09-13 Added newer definitions for network
2022-09-13 Added next incremental module
2022-09-14 Added the changes to RunFlexSpec to properly attach to a remotge machine
2022-09-15 Added CamMaths with the start of doc on the cam and algorithms
2022-09-21 Added correct tie to Rpi nginx server as proxy Removed detritis about prior trials
2022-09-26 Added the files for the documentation
2022-10-18 Hosed the UI, fixed the RunFlexSpec script
2022-10-21 added FlexCRC -- the counterpart of Arduino code.
2022-10-23 Added a few new fields, adjusted msgs
2022-10-23 Fixed things to make python script again, clear fixed
2022-10-23 Messageing and verbose flag.
2022-10-23 Removed stupid 100s delay
2022-10-23 Serial test with pretty json
2022-10-24 Added a git fixer for script files
2022-10-24 Added buttons, renamed to rst
2022-10-24 added things to gitignore gitattrbutes
2022-10-27 Added the FlexTextInput module, missed commit
2022-10-27 Initial checkin of statemachine code for server.
2022-10-27 Pulled out stupid delay
2022-10-28 Added a binary file manager lookahead/pushback
2022-10-30 Beefed up FlexCRC, test cases examples, rounting
2022-11-02 Cleaned up python and the doc/comments
2022-11-02 Incremental checkin
    The network was updated to be url based.
    The main flexspec has an Flex_Instrument instance, allows name change
    to be propagated.
    Added a few placeholder values -- need more
    Started removing the device name, need to put that back.
    This is a placeholder for the current work.
2022-11-02 Added code to make the process more robust
2022-11-06 Moving to new machine, incremental checkin
2022-11-07 Sliders, fixing initial start, SQL start
2022-11-08 Added coordinated text field, recents
2022-11-08 Merged functions, added on/off, save, restore stubs
2022-11-10 Added shutter, finessed the overall kzin layout and actions.
2022-11-16 Added a logger to the mix
2022-11-16 Instrument added to widgets, consistent json
2022-11-18 Smoothed out Publish protocol
2022-11-29 Unknown changes. Identical
2022-12-01 Leading to a tagged release
2023-01-05 Added the Rpi followme script
2023-01-13 Adding additional steps
2023-01-21 Added very basic usb/tty tests
2023-01-21 Script to find arduino TTY port
2023-01-21 Fixed accidental overwrite
2023-01-27 Script to find arduino tty port names
2023-02-16 Fix markdown link in rst file
2023-02-18 Hand fixed the file per Neil McBarnett's request.
2023-03-29 Added comment for sketch.
2023-04-04 Initial Checkin of FlexSpec1GUI
2023-05-25 Updated Trim
2023-05-25 Added findtrim to mix
2023-05-25 Bad bug fixed in trim.
2023-05-25 Fixed WCS update error.
2023-07-12 Update .readthedocs.yaml
    Added yaml file per readthedocs request. Uncommented build pdf
    ane epub.
2023-07-12 Update cad.rst
    Added Freecad mention and cleared up the explainations a bit.
2023-07-12 Update callamps.rst
    Updated for 2023 electronics
2023-07-12 Create Notes.txt
    Notes of more extensive cleanup/additions
2023-08-29 Added install file template
2023-08-29 Add a FollowMe.Stellarmate to feather clean install.
2023-08-29 Fiddling around with the yaml readthedocs file
2023-08-29 Added eof marker for end of file
2023-08-30 pyraf package spelled wrong
2023-08-30 StellarMate was spelled wrong
2023-08-30 git install had a type
2023-08-30 FlexSpec.install had wrong path
2023-08-30 Path changed and made executable
2023-08-31 Rename aliases
2023-08-31 Added adding aliases to the directory
2023-08-31 Fixed install of aliases
2023-08-31 Added filezilla to list for FlexSpec
2023-08-31 Added gawk to the mix
2023-08-31 Install IRAF independently
2023-08-31 Move IRAF install to separate script
2023-08-31 Tuned up git
2023-08-31 New git format
2023-08-31 Updated git repo locations
2023-09-02 review and tweaked files
2023-11-04 Added the XMing doc to the mix
2023-11-05 Better Document, and tex source code, images.
2023-11-10 Updated for Paramount
2023-11-12 Incremental check in
2023-11-16 Adding code to project
2023-11-16 fixed syntax
2023-11-16 Fixing doc
2023-11-16 The source code for the main FlexSpec1 Board.
2023-11-16 Cleaned up code, added support for development
2023-11-16 Added a directory for useful tools
2023-11-16 Cleaned up directory
2023-11-16 Cleaned up directory some more
2023-11-16 Updating Documentation
2023-11-16 Version 4.1
2023-11-16 Version 4.1.1
2023-11-16 Version 4.1.2
2023-11-16 Added BLE Baseboard V2 to the repo.
2023-11-16 Update text
2023-11-16 Added Xaio Standalone Board files.
2024-01-11 Borrowed PyRAF yaml
2024-01-17 Synch
2024-08-10 Create NewSystem.sh
    Prepare for new box
2025-04-15 Update README.rst
    Added the commands to the GitHub page for reference
